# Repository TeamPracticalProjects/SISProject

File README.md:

# SISOverview
SIS stands for "Standalone Intelligent Sensor" system. The documents in this repository provide everything you need to make and deploy your own SIS. You'll find concept documents, a FAQ, the firmware for your Arduino-like particle.io processor, printed circuit board files, parts lists, links to sources for all the parts, detailed assembly instructions, source code to a control web page, and a complete users guide. At Team Practical Projects we always make a complete project! And we know this repo is complete because, unknown to us, someone in Europe made one!

We are looking for people who are interested in building and using the SIS.  We are also interested in ideas for expanding the current SIS with additional useful features and we are open to  ideas for additional applications of the base SIS technology (some ideas are in the Concept document). SIS is an open source project and we are interested in improvements that other developers might wish makethemselves and/or to collaborate with us on.

If you want to use this project, download the Master branch. That is the currently released and well tested code.

If you have code to contribute, then generate a pull request for the Development branch. We don't want to take in pulls for master branch unless it is some critical issue with the current release.

We are two hobbyists who work on the SIS in our spare time. You don't have to be a hardcore, gung-ho, work on it until you drop, kind of person; we certainly aren't. Collaboration could just mean that you'd like to have one of these to install and test somewhere. We are open to make changes to the code to fit your need, as long as you provide us feedback on how it works and ideas on how to improve it.

We're currently working on three big things:
* Low power custom sensors... This project includes Arduino code to make your own wireless sensor, but running an Arduino requires regular power. We're working on using the ATTiny platform in power-down mode so we (you) could make any kind of low power sensor you want!
* Graphical output in the client... Thanks to a contributor in the Netherlands we are experimenting with the Google graph "Timeline". It provides a strip chart view of the sensor log. This is more usable than the current text list. If you want to help with this, let us know and we'll share that branch.

Of course collaboration could also mean that you want to add functions to the core firmware or javascript web site. That would be cool too.

The documentation is the best place to learn about the project. We starting a [Wiki](https://github.com/TeamPracticalProjects/SISProject/wiki/Wiki-Home) with little tips for new developers.

Send us a message to join in the fun: SISProject@shrimpware.com

Read about the SIS at other places on the web:
* [Hackster.io](https://www.hackster.io/PracticalProjects/standalone-intelligent-sensor-system-cbdb44)
* [Instructables](http://www.instructables.com/id/Standalone-Intelligent-Sensor-System/)

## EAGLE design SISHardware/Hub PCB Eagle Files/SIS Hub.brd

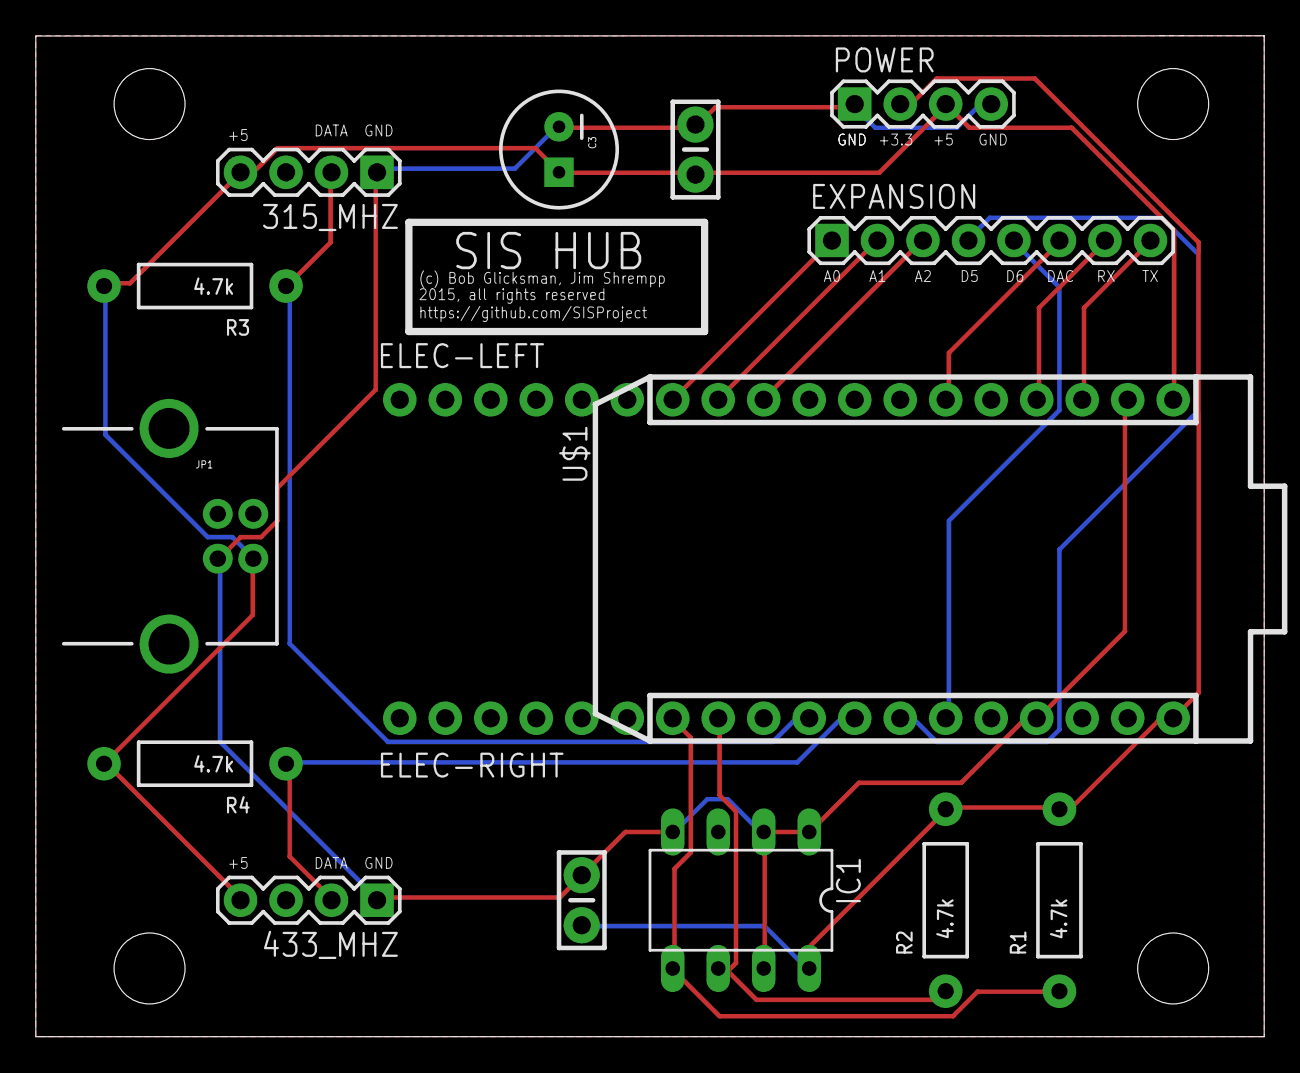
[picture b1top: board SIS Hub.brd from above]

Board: 2 copper layers, 68.6 x 55.9 mm, 16 parts (0 on the bottom side), 15 nets.

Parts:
315_MHZ, 433_MHZ: 1X04
C1, C2: 0.1uf; CAP-PTH-SMALL-KIT
C3: 100uf; CPOL-RADIAL-100UF-25V
ELEC-LEFT: 1X06_NO_SILK
ELEC-RIGHT: 1X06_NO_SILK
EXPANSION: 1X08
IC1: AT24LC256; DIL08
JP1: USB-B; USB-B-PTH
POWER: 1X04
R1, R2, R3, R4: 4.7k; AXIAL-0.4
U$1: PHOTON_WITH_HEADERS; PHOTON

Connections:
5V: 315_MHZ.4, 433_MHZ.4, C2.1, C3.1, JP1.VBUS, POWER.3, R3.P$2, R4.P$2, U$1.1
GND: 315_MHZ.1, 433_MHZ.1, C1.2, C2.2, C3.2, IC1.1, IC1.2, IC1.4, IC1.7, JP1.GND, POWER.1, POWER.4, U$1.2, U$1.21
unnamed: IC1.5, R1.P$1, U$1.13
unnamed: IC1.6, R2.P$1, U$1.14
unnamed: 315_MHZ.2, R3.P$1, U$1.16
unnamed: 433_MHZ.2, R4.P$1, U$1.17
unnamed: EXPANSION.1, U$1.12
unnamed: EXPANSION.4, U$1.18
unnamed: EXPANSION.8, U$1.3
unnamed: EXPANSION.7, U$1.4
unnamed: EXPANSION.6, U$1.6
unnamed: EXPANSION.3, U$1.10
unnamed: EXPANSION.2, U$1.11
unnamed: EXPANSION.5, U$1.19
VCC: C1.1, IC1.8, POWER.2, R1.P$2, R2.P$2, U$1.24

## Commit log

2015-06-04 SIS Overview Document
    Describes the SIS concept and specifications
2015-06-04 FAQ for the SIS Project
2015-06-09 new folders and readmes
2015-06-09 Version 8c
    This version of Saratoga SIS (08c) contains support for Photon and Core.
    There are patches for Particle problems with the Time and Wire
    libraries. These libraries are schedule to be fixed by Particle and
    these patches may then go obsolete.
2015-06-09 Readme for the branch
2015-06-10 as currently deployed
2015-06-11 moved original
2015-06-11 removing firmware2
2015-06-13 README updated to encourage people to contact us.
2015-06-26 updates to Elm config and to make sensors > 6 generic
2015-06-27 restored some missing eol spaces to make pull request cleaner.
2015-06-27 added comments to js. corrected description in html header
2015-06-29 removed message about refresh attrib error and made device select again work
2015-07-18 v8.0e adds generic trip sensor slots and an SIS alarm sensor position
2015-07-18 still v8.0e. Adds ifdef around the publish event that drives the web page.
2015-07-19 modifies sensor defaults for 4 and 10
2015-07-19 Added the reportFatalError routine to blink D7
2015-08-09 added back daily time sync, inside ifdefs for photon system v0.4.4
2015-08-09 now massage the circular buffer output to have local browser time
2015-08-09 added check of return value on spark.publish
2015-08-15 08h adds return code check of Spark.publish if running system firmware 0.4.4
2015-08-16 08i: now circular buffer entries are published to spark cloud no more than every four seconds
2015-08-16 just fixed some line starting tabs
2015-08-17 Bug fix to check Spark.publish return code before decrementing g_numToPublish. v08i1
2015-09-13 :tada: Added .gitattributes & .gitignore files
2015-09-17 Preliminary Versions Posted
    Preliminary versions of the Parts List and PCB Assembly Instructions are
    posted. These need review (by Jim) prior to being finalized to the
    Master branch for release.
2015-09-21 Update per Jim's review
    These documents are updated per Jim's review and the Parts List has been
    updated with the new, thinner box that Jim found.
2015-10-02 08i
    v08i adds blinks in Setup; I found them useful to know progress. Also
    tested return code in login at line 1389; if log to cloud fails, don’t
    decrement g_numToPublish.
2015-10-05 changes to pass JSLint (almost)
2015-10-05 device select is now a drop down list
2015-10-10 v18 uses ConfigPageCommon.html. Adds ConfigBigHouse
2015-10-10 still v18. Removed reference to rpi.css
2015-10-10 still v18. Added modal are-you-sure dialog for clearing config
2015-10-10 still v18. Changed layout to have Step 1-3 ahead of optional steps
2015-10-14 Increased the Wireless Sensor Array
    This version (08j) is based upon version 08i1. It increases the maximum
    number of wireless sensors to 20, of which 0-9 are considered PIR, 10-14
    are considered Door, and 15-19 are general purpose.
2015-10-27 version 19
2015-10-31 Preliminary SaratogaSIS09 Version
    This version supports the latest sensor configuration requirements (12
    PIRs). In limited, but preliminary testing, it seems to work fine. It
    is still lacking inverting the D7 LED state during setup().
2015-11-02 Complete Version 09
    This firmware version (a) inverts the D7 LED blinks so that D7 will be
    on if something hangs up in setup(); When D7 LED is off, setup() is
    complete and loop() has been entered. (b) increases sensors to 20 and
    implements the following sensor registration scheme:
    loc 0 - 11 are PIR (interior rooms)
    loc 12 - 15 are exterior door separation sensors
2015-11-05 moved a number of elements around. made buttons visible at all times and only enabled when the can be used.
2015-11-06 added generic sensors to Big House so all spots are available to use.
2015-11-07 v21 more layout changes
2015-11-07 v22 changed module name from SISTest to SISClient
2015-11-07 still v22. Updated web pages to new SISClient object name.
2015-11-07 still v22. Moved all style into a .css file. Removed outer div width to become responsive.
2015-11-07 still v22. more styling to the page.
2015-11-07 made realtime activity tighter
2015-11-07 still v22. Current sensor display now updates after configuration of a new sensor
2015-11-07 still v22. Sensor config info is now reset when the current SIS config is cleared.
2015-11-09 v23 Now with the sensor table as the main configuratin element
2015-11-09 still v23 Reset and Add are now disabled correctly. Modal div for adding is centered in viewport.
2015-11-09 still v23. Removed sensor select drop down.
2015-11-09 still v23. Removed showASensor
2015-11-09 still v23. Removed some external exposure to routines that are now just internal
2015-11-09 still v23. Removed unused DIVs from web site.
2015-11-09 v23 still. Realtime alerts are working again.
2015-11-09 still v23. Now tells SIS to save config whenever a device is configured or reset.
2015-11-10 still v23. changed order of Divs to put Commands above sensor table
2015-11-10 still v23. Changed sensor log output to have shorter style.
2015-11-10 still v23. When selecting a device, the sensor config is automatically retrieved and the sensor table is updated.
2015-11-10 still v23. Reworked the Add sensor pop up to have better buttons and text.
2015-11-14 still v23. Changed config name from BigHouse to ConfigStandard
2015-11-14 v24 fixed time display to match SIS UTCOffset when displaying sensor log
2015-11-14 still v24. Sensor table codes are now initially ? and updated to -- when the retrieval is in process.
2015-11-14 wording changes
2015-11-14 terms of use doc
2015-11-14 :confetti_ball: Added .gitattributes & .gitignore files
2015-11-14 SIS Hub PCB Files
    Added a directory to contain the SISHub PCB fils. The .brd and .sch
    file are age files. The others are pdf versions of these files.
2015-11-15 changes to debug page to make it work now.
2015-11-19 Release version 1.00
    Updated comments and cleaned out the history. Performed a minimal
    amount of prettying up, albeit I did not fix tabbing issues in the code.
2015-11-20 still v24. Fixed lookup of active device when one is selected in list; not sure why it ever worked. Also added error messages to handle case where cloud says device is online when the device is actua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
2015-11-20 still v24. restored the output that says 'end of sensor log' when the page is finished retieving them.
2015-11-20 added ToU
2015-11-20 added a readme
2015-11-20 removed ToU. It has been moved to SISDocs
2015-11-20 still v24. corrected link to GitHub project
2015-11-20 v26. Now expects SIS 1.00
2015-11-21 corrected github link
2015-11-21 still v26. Added Send of Sensor Buffer message when buffer holds 100 entries
2015-11-21 Posted Arduino Transmitter Code
2015-11-22 still v26. Another off by one error in retrieving sensor config.
2015-11-22 Posting release versions of these documents
    Updated and reviewed Concept and FAQ documents for the SIS release
2015-11-22 Release documents
    PDF versions of reviuewed documents for SIS release.
2015-11-22 Updated the README file for release
2015-11-22 Added a README files for the release
2015-11-22 Updared the README for the release
2015-11-22 Updated the README for the release
2015-11-22 Fixed heading for README
2015-11-22 Fixed README
    added "repository" (missing word).
2015-11-23 Corrected GitHub TOU reference
2015-11-23 Updated GitHub links
2015-11-23 Updated links
    Include reference to TOU document and RC-Switch license info
2015-11-23 Added SISProject @shrimpware.com e-mail to README
2015-11-24 added link to ToU
2015-11-29 Added Read Me First document
2015-12-01 Updated Read_Me_First
    Per Jim' comments
2015-12-01 Moved to Overview repository
2015-12-01 Moved from Docs repository
2015-12-15 functionalize toggling D7 LED
2015-12-15 allow the time in for the LEDs in toggleD7LED() to be adjustable
2015-12-15 create #define for controlling if toggleD7LED() actually functions
2015-12-19 initial dummy commit
2015-12-19 Cleanup initial file
2015-12-19 moved SISSoftware to new subdir
2015-12-19 moved SISDocs to new subfolder
2015-12-19 moved SISOverview to subfolder
2015-12-19 Moved SISHardware to subfolder
2015-12-19 moved overview docs to top level
2015-12-20 moved some docs back to SISOverview
2015-12-20 Moved read me first back to root
2015-12-20 update README.MD
    added note about working on the Development branch.
2015-12-21 moved arduino test code into new folders
2015-12-21 added testbeacon code
2015-12-21 moved the beacon code into setup() so that once it runs 100 iterations the device just blinks D7.
2015-12-29 Updated with new paths to TPP
2015-12-29 Updated links
2015-12-30 Updated inks
2015-12-30 Update links
2015-12-30 Update README.md
    added link to Hackster.io
2015-12-30 Update TOU link
    Also updated version to 1.01
2015-12-31 added comments to ISR and formatted code for ISR
2015-12-31 Revert "Merge pull request #1 from TeamPracticalProjects/master"
2016-01-02 reverted 88979a4 to get open_close_ix.ino back. Added TestBeacon.ino
2016-01-03 comments and format to ISR
2016-01-17 added comment to note that client depends upon the string 'unknown'
2016-03-27 removed duplicate return statement
2016-07-10 new doc
2016-11-20 Added wireless reception tips document

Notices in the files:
SISHardware/Hub PCB Eagle Files/SIS Hub.brd:
2015, all rights reserved
parts and their libraries:
SparkFun-Capacitors: Licensing: Creative Commons ShareAlike 4.0 International - https://creativecommons.org/licenses/by-sa/4.0
SparkFun-Connectors: Licensing: CC v3.0 Share-Alike You are welcome to use this library for commercial purposes.
